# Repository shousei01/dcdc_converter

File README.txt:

DCDC converter - LLC (isolated) + 4-switch buck-boost, STM32G474RBT3          Rev E2 (2026-10-20)
12-48 V in, 1.5-48 V / 5 A / 50 W out, basic isolation, isolated CAN

01_hardware
  kicad_project\   KiCad 6/7 project (10-sheet wired schematic + routed 4-layer PCB). Open in KiCad, or import
                   into EasyEDA Pro (File > Import > KiCad) - same files as easyeda\*.zip
  easyeda\         DCDC_LLC_4SBB_G474_EasyEDA_import.zip
  docs\            DCDC_Design_Notes.docx / .pdf (design notes: sizing, full scales, firmware notes, review),
                   schematic PDF, PCB layer PDF, DRC report, pin-map.xlsx (every MCU pin + all AFs + what we use),
                   T1_PQ2620_winding_guide.html (hand-winding guide, 2D/3D, dots), layout_review_layers.png
  fabrication\     JLCPCB Gerber/drill zip, CPL (pick & place), JLCPCB BOM;
                   DCDC_JLC_BOM.csv / DCDC_JLC_CPL.csv = assembly upload files (U1, T1, connectors, headers,
                   SW1 and the J6 SWD pads are hand-soldered / not placed and left out)
  bom\             grouped BOM with prices / sources
02_firmware        firmware workspace + README (pin map, clocks, ADC full scales, VIN monitor, OVP, start-up)
03_calculations    loss / LLC sizing scripts; aux_fuse_check.py (Rev D); flyback_aux.py (Rev E isolated aux
                   flyback: rail budget, DCM operating points, stresses, ripple, feedback); copper_check.py
                   (Rev E copper widths / losses of the high-current paths on the finished board)
04_scripts         generator, routing and clean-up scripts that build this release (Rev E layout: 04_scripts\pcb5)

Rev E2 changes (20 Oct)
  - Debug-port series resistors: R123-R128 47.5 Ohm 0402 (UNI-ROYAL 0402WGF475JTCE, C82290) in SWDIO, SWCLK,
    TP_DAC, TP_GPIO1, TP_GPIO2, NRST; R129 2 Ohm 0603 (FOJAN FRC0603F2R00TS, C2933191) from +3V3 to J6 pin 7 /
    J7 VTref (net PROG_3V3). Each sits on the MCU side of the J6 / J7 branch, put into the existing traces.
  - DRC clean-up: the 16 courtyard overlaps Rev E accepted (T1 / CR1-CR6 / R64, T2 / D8 / C94 / R116 / C95 /
    Q11 / R114, C98 / R122, C69 / U11, C34 / U1) are cleared by 0.05-2 mm moves with the tracks re-attached;
    the 4 silk-over-pad notices are gone too. DRC: 0 errors, 0 warnings, 0 unconnected (docs\DRC_report.txt).
  - Board-edit scripts: 04_scripts\pcb6 (build_e2.sh lists the order).

Rev E changes
  - Isolated aux supply: the isolator's built-in 3.3 V is gone. New flyback (sheet "Isolated aux flyback"):
    UC3843B U20 from +10V_P, FDN86246 Q11, PA3855.006NLT EP13 transformer T2 (Np:Ns 1.33:1, 2250 Vdc hi-pot),
    SS110 D9 -> isolated +10 V. Secondary regulation: TL431 U22 (+10 V = 9.98 V) driving an EL357N opto U21
    into the UC3843 COMP pin; RCD clamp D8/R116/C94; 2 A primary current limit (R114 0.5 Ohm).
  - Secondary rails now come from the flyback, not VBUS: +10 V (drivers) -> U4 LMR16006 10 V -> 5 V ->
    U5 TLV75533 -> +3V3 (MCU, CAN, isolator side B) -> FB1 -> +3V3A. The MCU, CAN and drivers are up as soon
    as VIN is present, before the LLC starts.
  - U12 is now a CA-IS3742LW (4-channel isolator, no power). U12 ENA = +5V_P, ENB = +3V3.
  - VREF+ back to +3V3A (3.3 V); REF3030 U19 removed. Full scales: VBUS / VOUT 68.0 V, IL +/-20.6 A
    (zero 1.65 V), IOUT 6.6 A, DAC3 / COMP 0-3.3 V (see design notes and 02_firmware README).
  - PCB re-placed and re-routed for 1 oz outer / 0.5 oz inner copper: power on F.Cu pours (one net each),
    In1 solid ground planes (GNDP / GND / GND_ISO) with 4 mm isolation bands, VBUS link / VOUT strip / PGND bar
    copy on B.Cu, signals on In2 / B.Cu under ground floods. Gate loops as tight HO + HS pairs (0.4 mm) on
    B.Cu / In2; power via fields at 1.7 mm pitch so In1 keeps a ground web; own GND via on every small R/C in the
    MCU area. Board copper loss ~0.5 W at 50 W / 12 V in (03_calculations\copper_check.txt).
PCB status: 160 x 105 mm, 4 layers, 291 footprints, 779 vias; 0 DRC errors / 0 warnings / 0 unconnected with the
JLC rules loaded (docs\DRC_report.txt); no copper in the primary-secondary or CAN bands.
Order: 4 layers, 1.6 mm, 1 oz outer / 0.5 oz inner copper, JLC04161H-7628 stack-up;
upload fabrication\*_gerbers_JLCPCB.zip, DCDC_JLC_BOM.csv and DCDC_JLC_CPL.csv.
New parts to check in the JLC placement viewer: U20 (SOIC-8), U21 (SOP-4), U22 (SOT-23), Q11 (SOT-23),
T2 (EP13 SMD), U12 (SOIC-16W), U5 (SOT-23-5).

Rev D changes (history)
  - NTC moved PA4 -> PA6 (ADC2_IN3); PA4 kept free for DAC1_OUT1
  - 10k pull-down to GND on every unused MCU pin (R90-R105; R93 is now the PA2 / VIN_PWM pull-down)
  - HSE crystal 16 MHz (Y1 + 12 pF C0G)
  - (superseded in Rev E) ADC / DAC / comparator reference: external REF3030 (U19, 3.000 V +/-0.2 %) on VREF+, no longer the
    isolator's 3.3 V rail. Full scales: VBUS / VOUT 61.8 V, IL +/-18.75 A, IOUT 6.0 A (see design notes)
  - Primary input OVP: TL431 + LMV331, trips 50.26 V rising / 49.83 V falling, through U12 isolator
    channel 1 -> PA15 (HRTIM1_FLT2)
  - Isolated VIN monitor: primary ramp (~200 Hz) + comparator PWM through U12 channel 2 -> PA2 (TIM15_CH1);
    divider R81/R82 0.1 %. Monitoring only, about +/-0.5 % after a two-point calibration
  - Test pads TP1-TP15 on rails / filtered signals only (no switch nodes)
  - T1 footprint fits the vendor PQ2620 and PQ2625 6+6 bobbins: 3.8 mm pitch inside each 3-pin group,
    7.5 mm between pins 3 and 4, 25.4 mm row-to-row, 1.2 mm holes
  - JP1 is a 2x2 header that switches both legs of the CAN split termination
  - Silkscreen: VIN+/-, VOUT+/-, CAN_H / CAN_L / CAN_GND, JP1 shunt boxes, J7 notch + pin 1, DIP A0-A5 / ON=1
  - F1 now a 1206 7 A 63 V chip fuse (Littelfuse 0458007.DR; 2nd source Schurter 3413.0326.11);
    L2 / L3 now 5040 shielded 47 uH (Sunlord SWPA5040S470MT; 2nd source Bourns SRN5040-470M,
    Taiyo Yuden NRS5040T470MMGK). EN_AUX re-routed, VIN track centred between the L3 pads.
    Every part carries a JLCPCB-checked LCSC number (design.py JLC_LCSC) in the BOMs, schematic and PCB
  - Layout review (18 Oct): smaller switch-node pours, tighter gate loops, Kelvin taps, output pour,
    straightened routing, 5 mm ground stitching
  - JLCPCB compliance (4-layer, 2 oz outer): PTH pad-to-track >= 0.28 mm, inner hole-to-copper >= 0.3 mm,
    silkscreen text >= 1.0 mm / 0.15 mm stroke; limits kept as custom DRC rules in kicad_project\*.kicad_dru
Rev D PCB status: 160 x 105 mm, 4 layers, 257 footprints, 0 DRC errors / warnings with the JLC rules loaded,
0 unconnected, primary-secondary copper gap 4.0 mm on every layer.
Rev D order: 4 layers, 1.6 mm, 2 oz outer copper, JLC04161H-7628 stack-up; upload fabrication\*_gerbers_JLCPCB.zip.

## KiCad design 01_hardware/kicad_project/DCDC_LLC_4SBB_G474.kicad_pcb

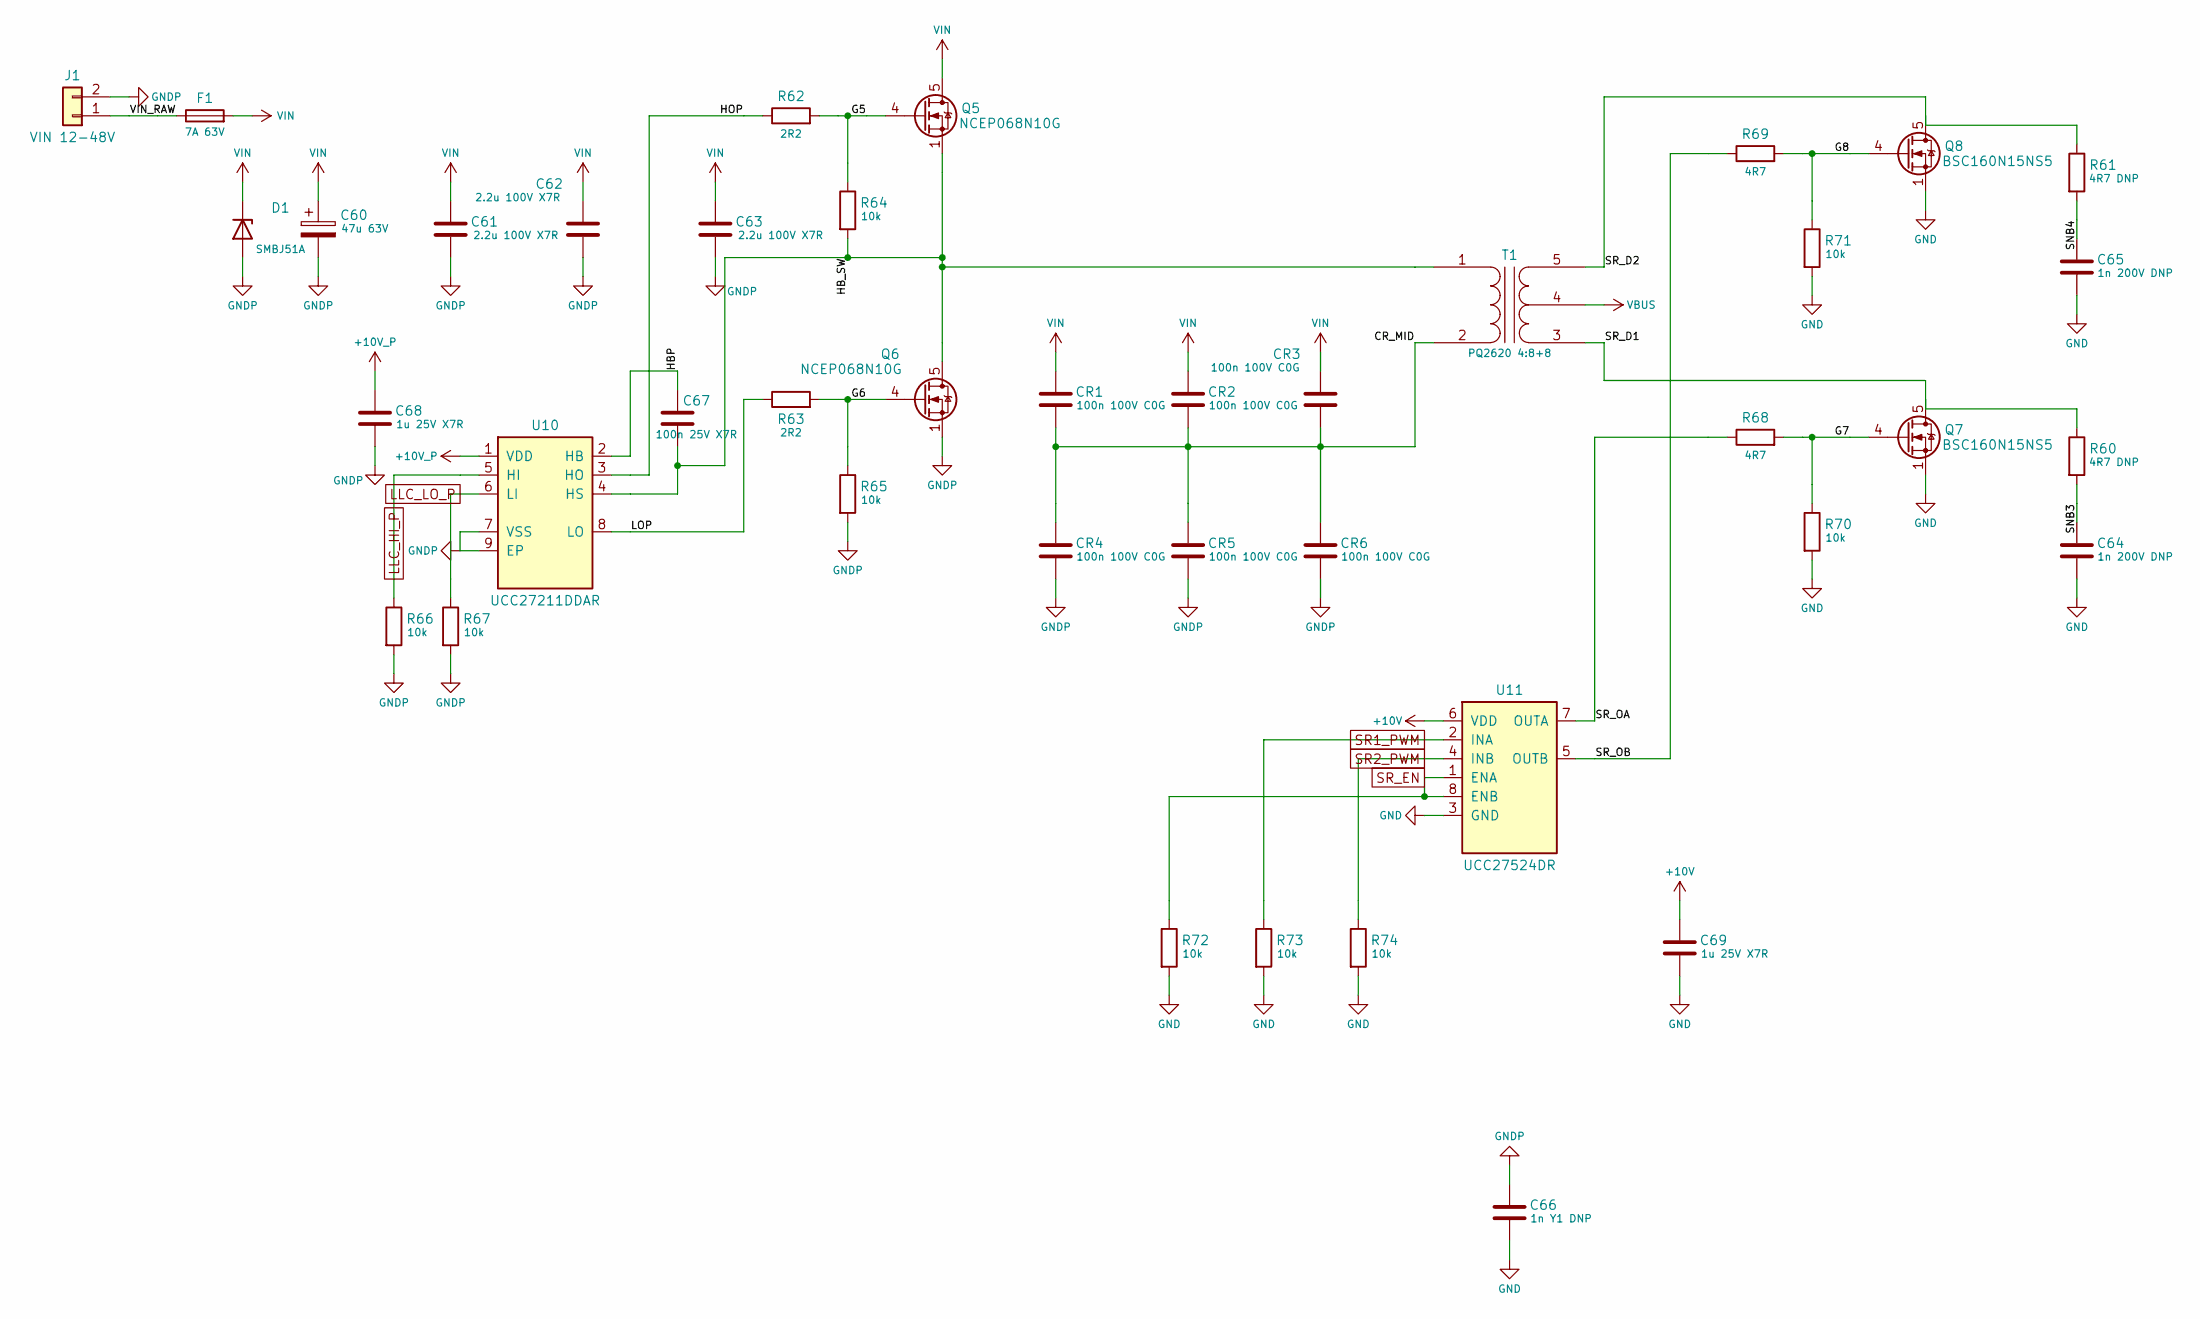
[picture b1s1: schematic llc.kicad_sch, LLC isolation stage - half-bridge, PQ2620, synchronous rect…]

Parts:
C60: 47u 63V; CP_Elec_10x10.5; MPN 47u 63V; LCSC C249664
C61, C62, C63: 2.2u 100V X7R; C_1210_3225Metric; MPN 2.2u 100V X7R; LCSC C153036
C64, C65: 1n 200V DNP; C_0805_2012Metric; MPN 1n 200V DNP
C66: 1n Y1 DNP; C_Disc_D8.0mm_W5.0mm_P7.50mm; MPN 1n Y1 DNP
C67: 100n 25V X7R; C_0603_1608Metric; MPN 100n 25V X7R; LCSC C14663
C68, C69: 1u 25V X7R; C_0603_1608Metric; MPN 1u 25V X7R; LCSC C15849
CR1, CR2, CR3, CR4, CR5, CR6: 100n 100V C0G; C_1206_3216Metric; MPN 100n 100V C0G; LCSC C2940749
D1: SMBJ51A; D_SMB; MPN SMBJ51A; LCSC C20883337
F1: 7A 63V; Fuse_1206_3216Metric; MPN 0458007.DR; LCSC C206980
J1: VIN 12-48V; PhoenixContact_MSTBA_2,5_2-G-5,08_1x02_P5.08mm_Horizontal; MPN KF2EDGR-5.08-2P; LCSC C441204
Q5, Q6: NCEP068N10G; TDSON-8-1; MPN NCEP068N10G; LCSC C503061
Q7, Q8: BSC160N15NS5; TDSON-8-1; MPN BSC160N15NS5; LCSC C459172
R60, R61: 4R7 DNP; R_1206_3216Metric; MPN 4R7 DNP
R62, R63: 2R2; R_0603_1608Metric; MPN 2R2; LCSC C2907006
R64, R65, R66, R67, R70, R71, R72, R73, R74: 10k; R_0402_1005Metric; MPN 10k; LCSC C2906861
R68, R69: 4R7; R_0603_1608Metric; MPN 4R7; LCSC C23164
T1: PQ2620 4:8+8; TX_PQ2620_12P; MPN PQ2620 4:8+8
U10: UCC27211DDAR; SOIC-8-1EP_3.9x4.9mm_P1.27mm_EP2.41x3.3mm; MPN UCC27211DDAR; LCSC C141980
U11: UCC27524DR; SOIC-8_3.9x4.9mm_P1.27mm; MPN UCC27524DR; LCSC C465729

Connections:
+10V: C69.1, U11.6 (VDD); also elsewhere on the board
+10V_P: C68.1, U10.1 (VDD); also elsewhere on the board
CR_MID: CR1.2, CR2.2, CR3.2, CR4.1, CR5.1, CR6.1, T1.2 (AB)
G5: Q5.4 (G), R62.2, R64.1
G6: Q6.4 (G), R63.2, R65.1
G7: Q7.4 (G), R68.2, R70.1
G8: Q8.4 (G), R69.2, R71.1
GND: C64.2, C65.2, C66.2, C69.2, Q7.1 (S), Q7.2 (S), Q7.3 (S), Q8.1 (S), Q8.2 (S), Q8.3 (S), R70.2, R71.2, R72.2, R73.2, R74.2, U11.3 (GND); also elsewhere on the board
GNDP: C60.2, C61.2, C62.2, C63.2, C66.1, C68.2, CR4.2, CR5.2, CR6.2, D1.2 (A), J1.2, Q6.1 (S), Q6.2 (S), Q6.3 (S), R65.2, R66.2, R67.2, U10.7 (VSS), U10.9 (EP); also elsewhere on the board
HBP: C67.1, U10.2 (HB)
HB_SW: C67.2, Q5.1 (S), Q5.2 (S), Q5.3 (S), Q6.5 (D), R64.2, T1.1 (AA), U10.4 (HS)
HOP: R62.1, U10.3 (HO)
LLC_HI_P: R66.1, U10.5 (HI); also elsewhere on the board
LLC_LO_P: R67.1, U10.6 (LI); also elsewhere on the board
LOP: R63.1, U10.8 (LO)
SNB3: C64.1, R60.2
SNB4: C65.1, R61.2
SR1_PWM: R73.1, U11.2 (INA); also elsewhere on the board
SR2_PWM: R74.1, U11.4 (INB); also elsewhere on the board
SR_D1: Q7.5 (D), R60.1, T1.3 (SA)
SR_D2: Q8.5 (D), R61.1, T1.5 (SB)
SR_EN: R72.1, U11.1 (ENA), U11.8 (ENB); also elsewhere on the board
SR_OA: R68.1, U11.7 (OUTA)
SR_OB: R69.1, U11.5 (OUTB)
VBUS: T1.4 (SC); also elsewhere on the board
VIN: C60.1, C61.1, C62.1, C63.1, CR1.1, CR2.1, CR3.1, D1.1 (K), F1.2, Q5.5 (D); also elsewhere on the board
VIN_RAW: F1.1, J1.1

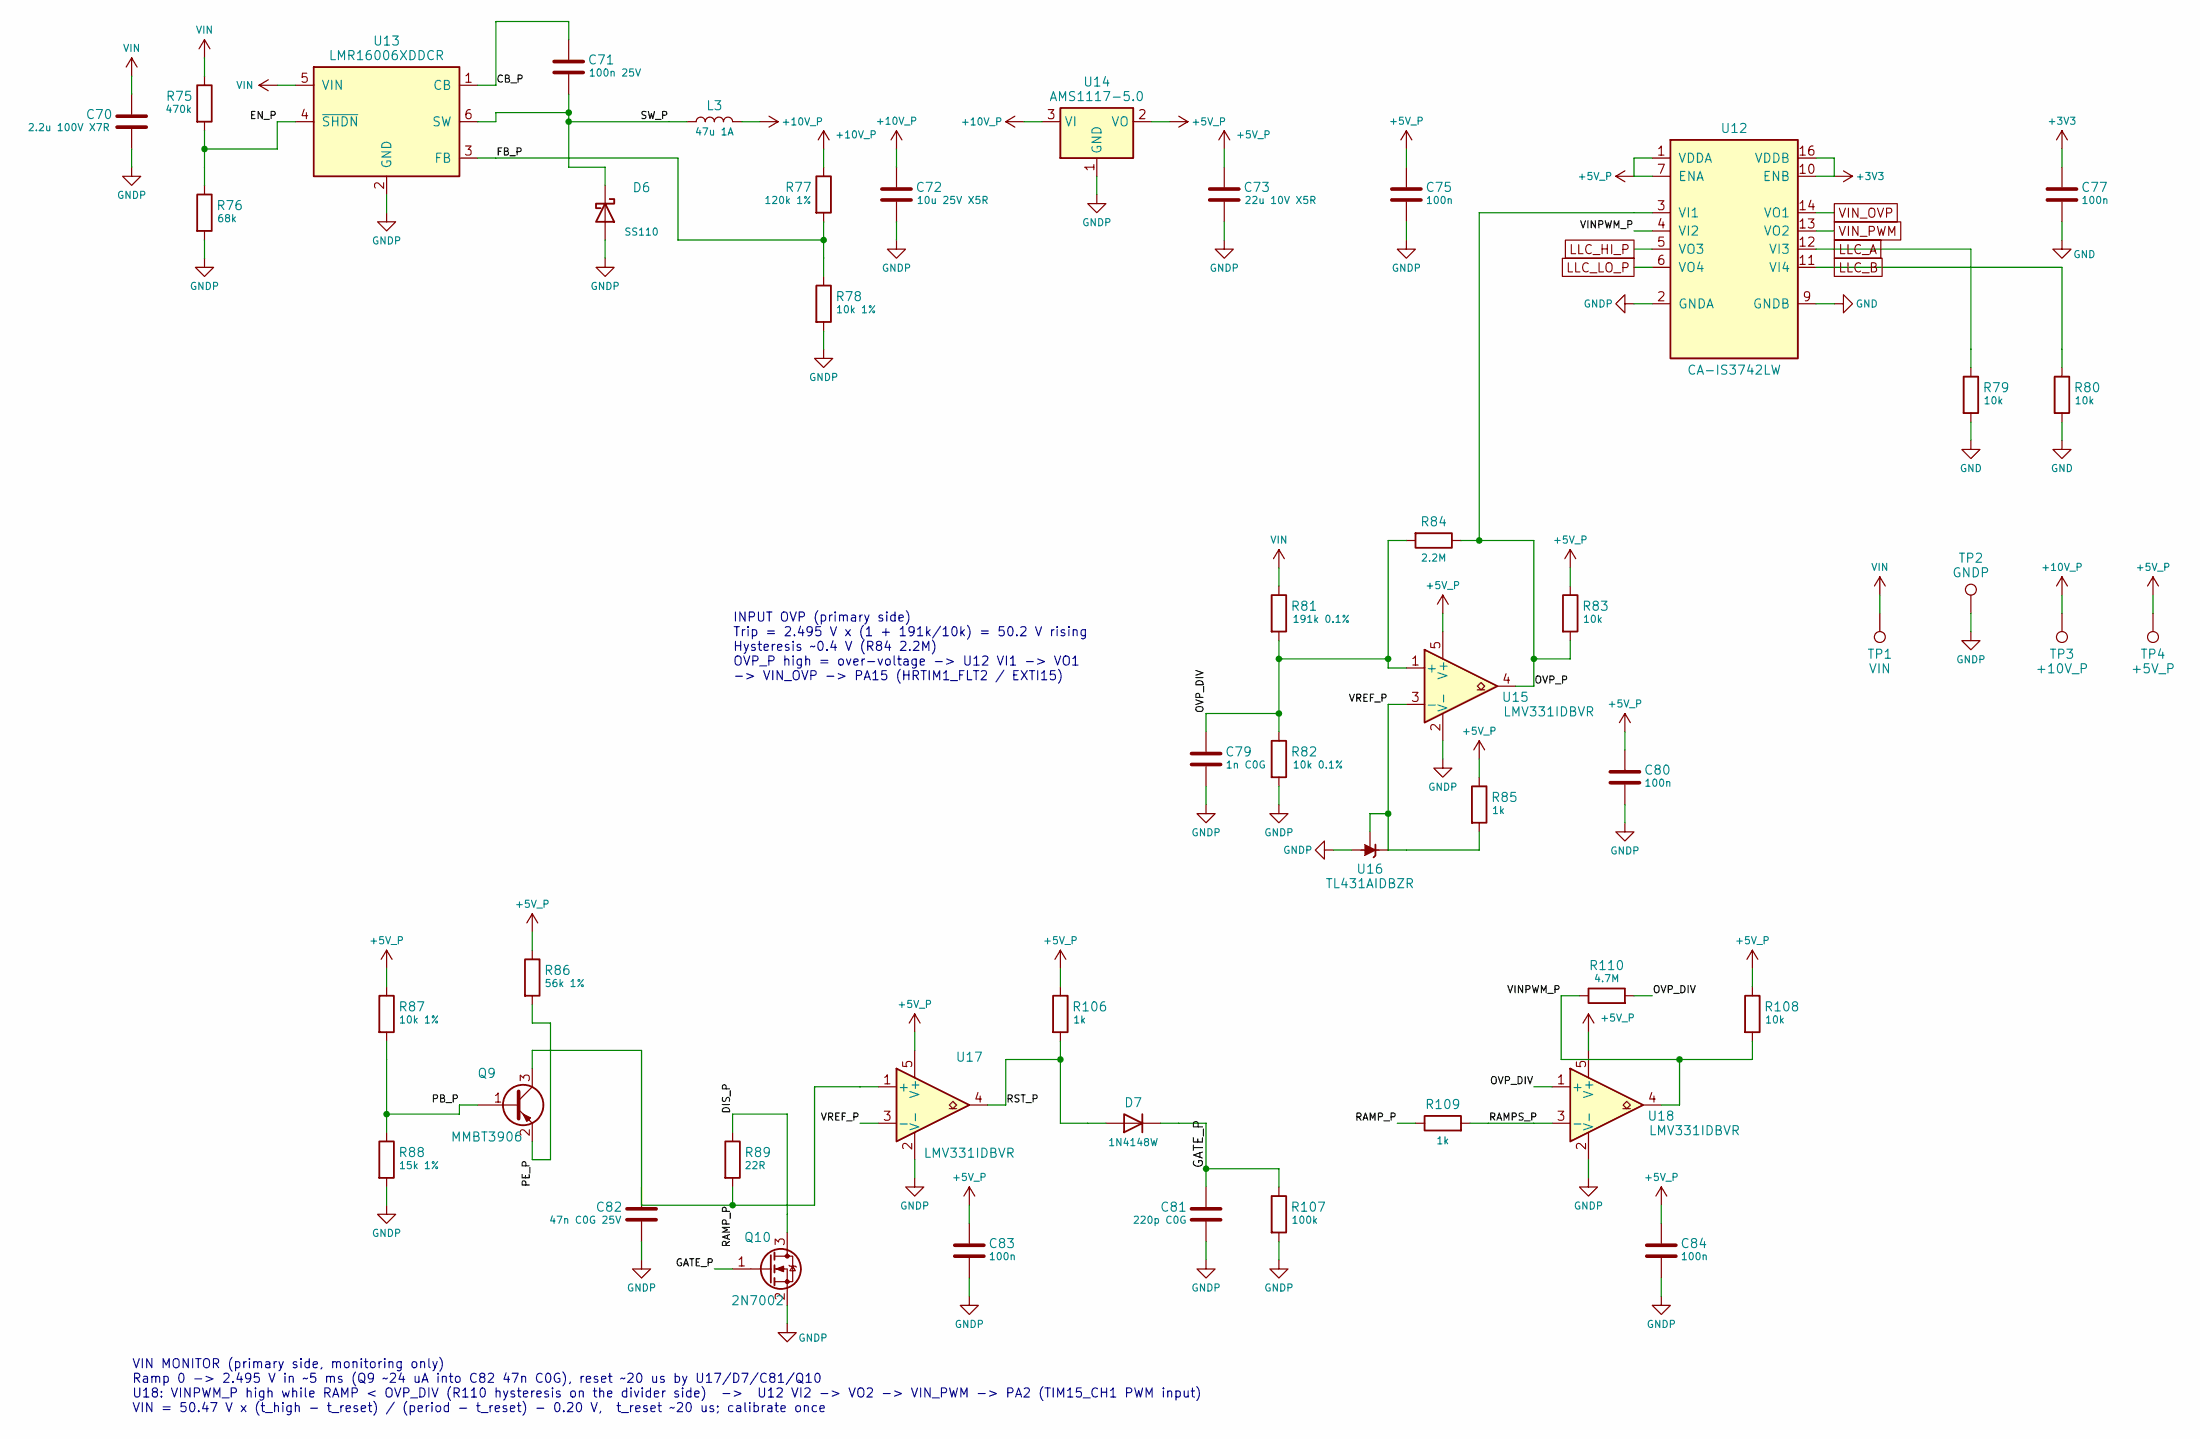
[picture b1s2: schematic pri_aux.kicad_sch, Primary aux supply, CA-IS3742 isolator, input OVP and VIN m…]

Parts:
C70: 2.2u 100V X7R; C_1210_3225Metric; MPN 2.2u 100V X7R; LCSC C153036
C71: 100n 25V; C_0402_1005Metric; MPN 100n 25V; LCSC C307331
C72: 10u 25V X5R; C_0805_2012Metric; MPN 10u 25V X5R; LCSC C15850
C73: 22u 10V X5R; C_0805_2012Metric; MPN 22u 10V X5R; LCSC C45783
C75, C77, C80, C83, C84: 100n; C_0402_1005Metric; MPN 100n; LCSC C307331
C79: 1n C0G; C_0402_1005Metric; MPN 1n C0G; LCSC C113780
C81: 220p C0G; C_0402_1005Metric; MPN 220p C0G; LCSC C107001
C82: 47n C0G 25V; C_0805_2012Metric; MPN C0805C473F3GECAUTO; LCSC C2233314
D6: SS110; D_SMA; MPN SS110; LCSC C2482
D7: 1N4148W; D_SOD-123; MPN 1N4148W; LCSC C81598
L3: 47u 1A; L_Sunlord_SWPA5040S; MPN FNR5040S470MT; LCSC C167974
Q9: MMBT3906; SOT-23; MPN MMBT3906; LCSC C53444
Q10: 2N7002; SOT-23; MPN 2N7002; LCSC C8545
R75: 470k; R_0603_1608Metric; MPN 470k; LCSC C23178
R76: 68k; R_0402_1005Metric; MPN 68k; LCSC C36871
R77: 120k 1%; R_0402_1005Metric; MPN 120k 1%; LCSC C25750
R78, R87: 10k 1%; R_0402_1005Metric; MPN 10k 1%; LCSC C2906861
R79, R80, R83, R108: 10k; R_0402_1005Metric; MPN 10k; LCSC C2906861
R81: 191k 0.1%; R_1206_3216Metric; MPN 191k 0.1%; LCSC C870479
R82: 10k 0.1%; R_0402_1005Metric; MPN 10k 0.1%; LCSC C844452
R84: 2.2M; R_0402_1005Metric; MPN 2.2M; LCSC C11490
R85, R106, R109: 1k; R_0402_1005Metric; MPN 1k; LCSC C11702
R86: 56k 1%; R_0402_1005Metric; MPN 56k 1%; LCSC C25796
R88: 15k 1%; R_0402_1005Metric; MPN 15k 1%; LCSC C25756
R89: 22R; R_0402_1005Metric; MPN 22R; LCSC C2929994
R107: 100k; R_0402_1005Metric; MPN 100k; LCSC C25741
R110: 4.7M; R_0402_1005Metric; MPN 4.7M; LCSC C227116
TP1: VIN; TestPoint_Pad_D1.5mm; MPN PCB pad, no part
TP2: GNDP; TestPoint_Pad_D1.5mm; MPN PCB pad, no part
TP3: +10V_P; TestPoint_Pad_D1.5mm; MPN PCB pad, no part
TP4: +5V_P; TestPoint_Pad_D1.5mm; MPN PCB pad, no part
U12: CA-IS3742LW; SOIC-16W_7.5x10.3mm_P1.27mm; MPN CA-IS3742LW; LCSC C4944981
U13: LMR16006XDDCR; SOT-23-6; MPN LMR16006XDDCR; LCSC C87080
U14: AMS1117-5.0; SOT-223-3_TabPin2; MPN AMS1117-5.0; LCSC C6187
U15, U17, U18: LMV331IDBVR; SOT-23-5; MPN LMV331IDBVR; LCSC C34731
U16: TL431AIDBZR; SOT-23; MPN TL431AIDBZR (TI pinout: 1 K, 2 REF, 3 A); LCSC C23892

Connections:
+3V3: C77.1, U12.10 (ENB), U12.16 (VDDB); also elsewhere on the board
+5V_P: C73.1, C75.1, C80.1, C83.1, C84.1, R83.1, R85.1, R86.1, R87.1, R106.1, R108.1, TP4.1, U12.1 (VDDA), U12.7 (ENA), U14.2 (VO), U15.5 (V+), U17.5 (V+), U18.5 (V+)
+10V_P: C72.1, L3.2, R77.1, TP3.1, U14.3 (VI); also elsewhere on the board
CB_P: C71.1, U13.1 (CB)
DIS_P: Q10.3 (D), R89.1
EN_P: R75.2, R76.1, U13.4 (~SHDN)
FB_P: R77.2, R78.1, U13.3 (FB)
GATE_P: C81.1, D7.1 (K), Q10.1 (G), R107.1
GND: C77.2, R79.2, R80.2, U12.9 (GNDB), U12.15 (GNDB); also elsewhere on the board
GNDP: C70.2, C72.2, C73.2, C75.2, C79.2, C80.2, C81.2, C82.2, C83.2, C84.2, D6.2 (A), Q10.2 (S), R76.2, R78.2, R82.2, R88.2, R107.2, TP2.1, U12.2 (GNDA), U12.8 (GNDA), U13.2 (GND), U14.1 (GND), U15.2 (V-), U16.3 (A), U17.2 (V-), U18.2 (V-); also elsewhere on the board
LLC_A: R79.1, U12.12 (VI3); also elsewhere on the board
LLC_B: R80.1, U12.11 (VI4); also elsewhere on the board
LLC_HI_P: U12.5 (VO3); also elsewhere on the board
LLC_LO_P: U12.6 (VO4); also elsewhere on the board
OVP_DIV: C79.1, R81.2, R82.1, R84.2, R110.2, U15.1 (+), U18.1 (+)
OVP_P: R83.2, R84.1, U12.3 (VI1), U15.4
PB_P: Q9.1 (B), R87.2, R88.1
PE_P: Q9.2 (E), R86.2
RAMPS_P: R109.2, U18.3 (-)
RAMP_P: C82.1, Q9.3 (C), R89.2, R109.1, U17.1 (+)
RST_P: D7.2 (A), R106.2, U17.4
SW_P: C71.2, D6.1 (K), L3.1, U13.6 (SW)
VIN: C70.1, R75.1, R81.1, TP1.1, U13.5 (VIN); also elsewhere on the board
VINPWM_P: R108.2, R110.1, U12.4 (VI2), U18.4
VIN_OVP: U12.14 (VO1); also elsewhere on the board
VIN_PWM: U12.13 (VO2); also elsewhere on the board
VREF_P: R85.2, U15.3 (-), U16.1 (K), U16.2 (REF), U17.3 (-)

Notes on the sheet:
INPUT OVP (primary side) Trip = 2.495 V x (1 + 191k/10k) = 50.2 V rising Hysteresis ~0.4 V (R84 2.2M) OVP_P high = over-voltage -> U12 VI1 -> VO1 -> VIN_OVP -> PA15 (HRTIM1_FLT2 / EXTI15)
VIN MONITOR (primary side, monitoring only) Ramp 0 -> 2.495 V in ~5 ms (Q9 ~24 uA into C82 47n C0G), reset ~20 us by U17/D7/C81/Q10 U18: VINPWM_P high while RAMP < OVP_DIV (R110 hysteresis on the divider side) -> U12 VI2 -> VO2 -> VIN_PWM -> PA2 (TIM15_CH1 PWM input) VIN = 50.47 V x (t_high - t_res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

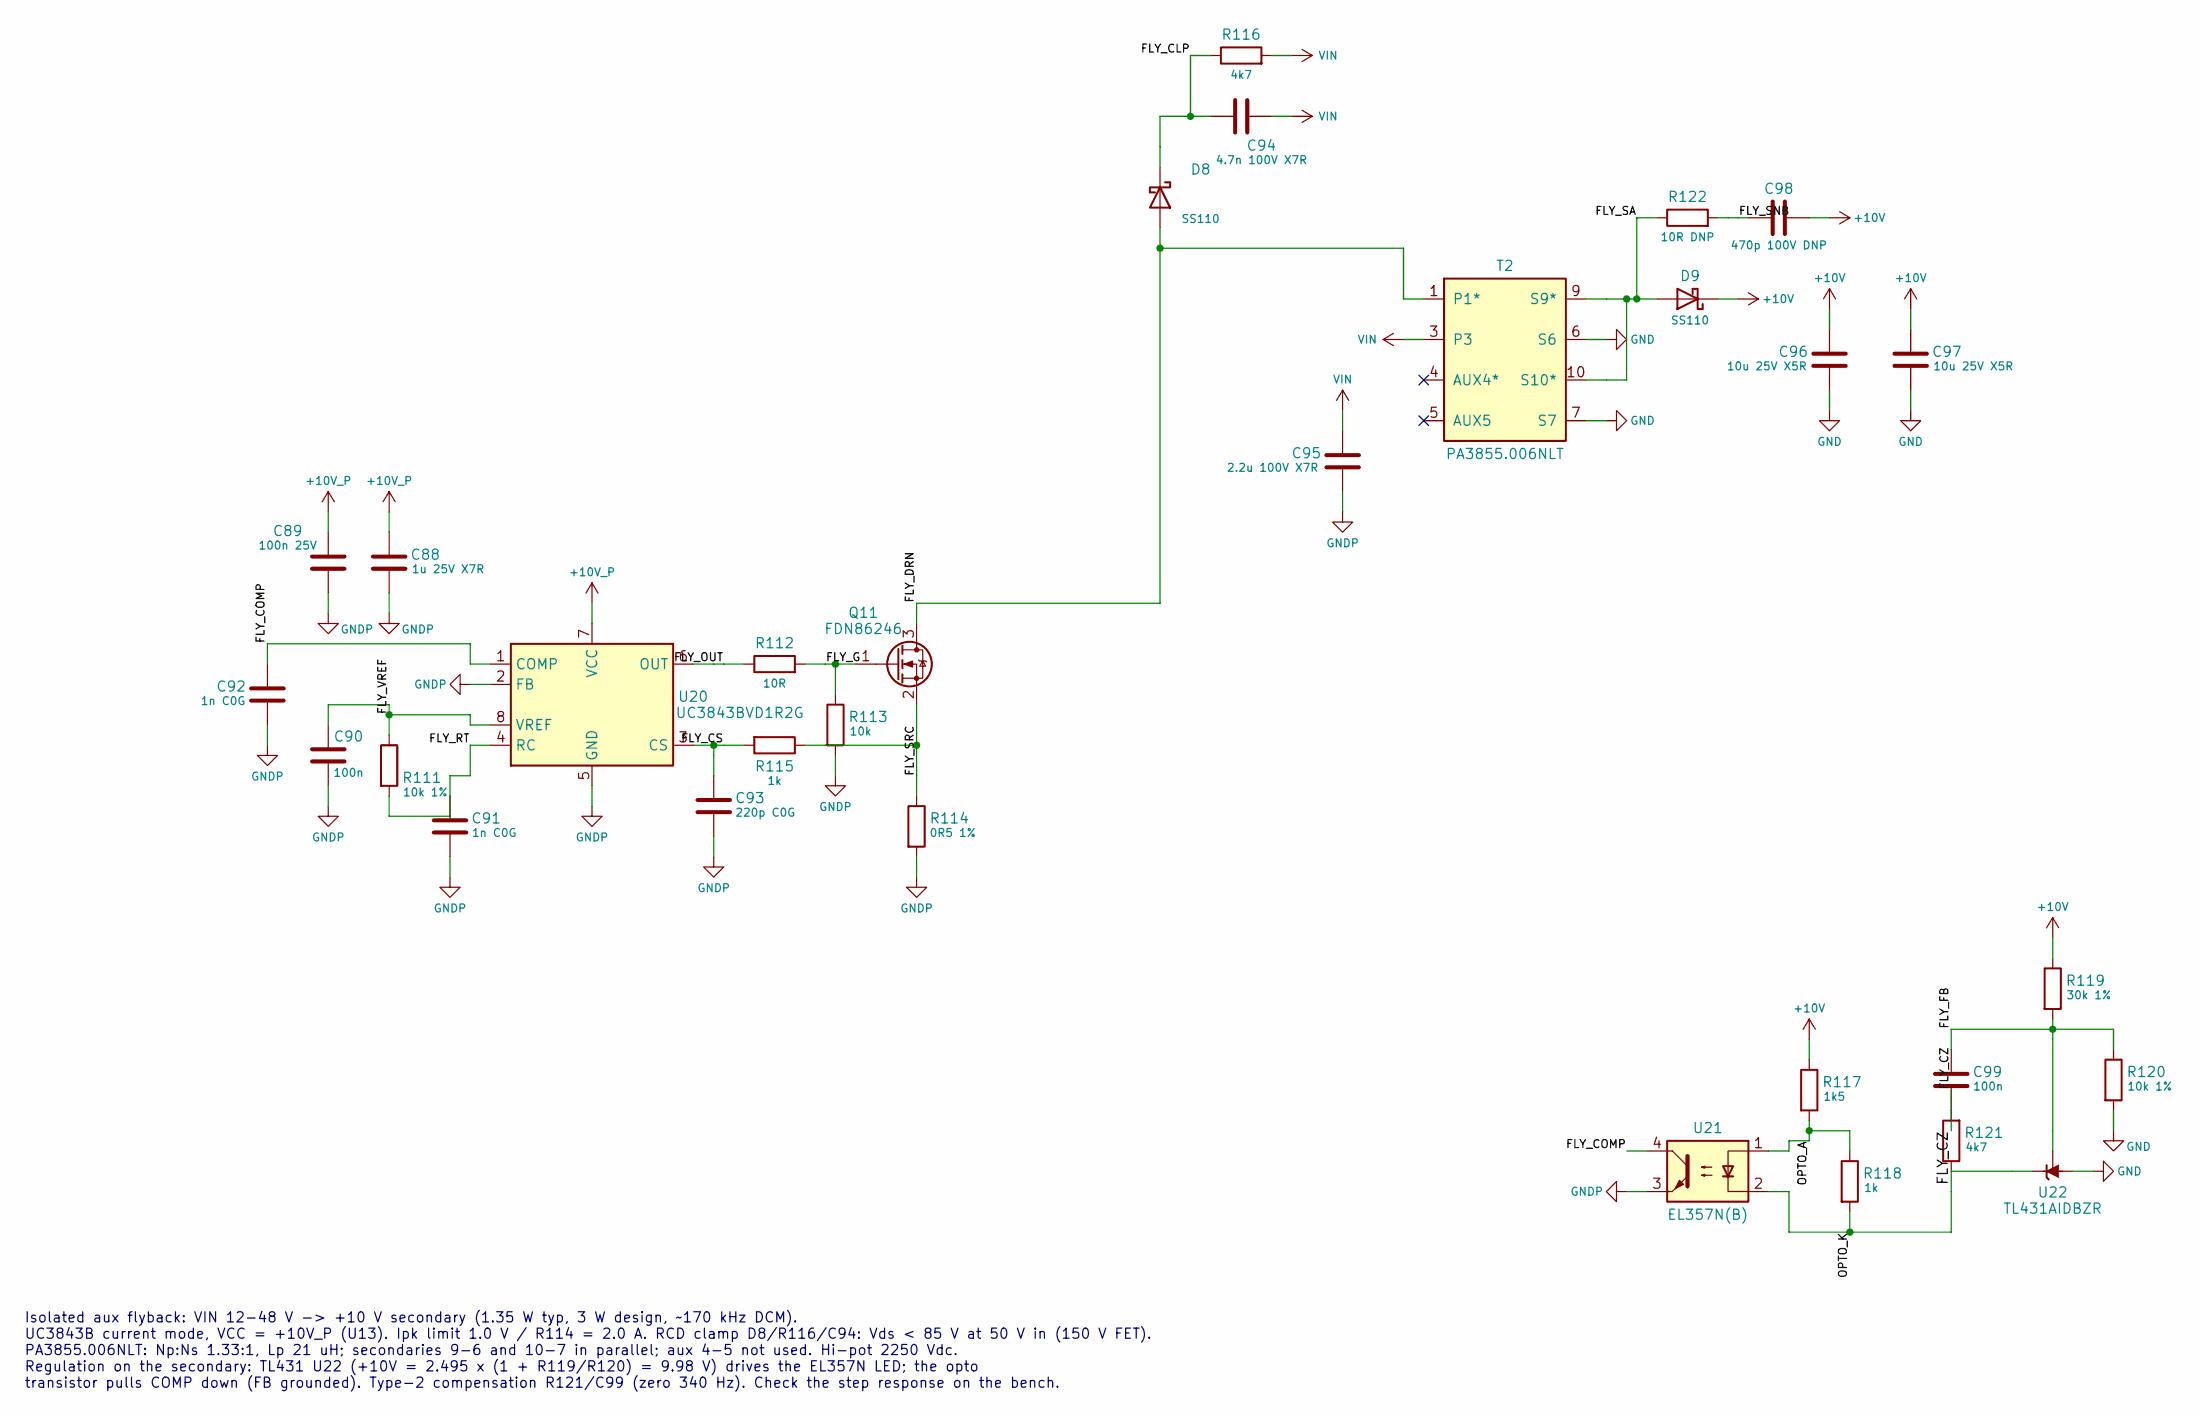
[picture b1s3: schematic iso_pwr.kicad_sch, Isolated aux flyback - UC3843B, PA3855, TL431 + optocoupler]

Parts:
C88: 1u 25V X7R; C_0603_1608Metric; MPN 1u 25V X7R; LCSC C15849
C89: 100n 25V; C_0402_1005Metric; MPN 100n 25V; LCSC C307331
C90, C99: 100n; C_0402_1005Metric; MPN 100n; LCSC C307331
C91, C92: 1n C0G; C_0402_1005Metric; MPN 1n C0G; LCSC C113780
C93: 220p C0G; C_0402_1005Metric; MPN 220p C0G; LCSC C107001
C94: 4.7n 100V X7R; C_0603_1608Metric; MPN 4.7n 100V X7R; LCSC C115052
C95: 2.2u 100V X7R; C_1210_3225Metric; MPN 2.2u 100V X7R; LCSC C153036
C96, C97: 10u 25V X5R; C_0805_2012Metric; MPN 10u 25V X5R; LCSC C15850
C98: 470p 100V DNP; C_0603_1608Metric; MPN 470p 100V DNP
D8, D9: SS110; D_SMA; MPN SS110; LCSC C2482
Q11: FDN86246; SOT-23; MPN FDN86246; LCSC C891118
R111, R120: 10k 1%; R_0402_1005Metric; MPN 10k 1%; LCSC C2906861
R112: 10R; R_0603_1608Metric; MPN 10R; LCSC C22859
R113: 10k; R_0402_1005Metric; MPN 10k; LCSC C2906861
R114: 0R5 1%; R_1206_3216Metric; MPN 0R5 1%; LCSC C25340
R115, R118: 1k; R_0402_1005Metric; MPN 1k; LCSC C11702
R116: 4k7; R_1206_3216Metric; MPN 4k7; LCSC C17936
R117: 1k5; R_0402_1005Metric; MPN 1k5; LCSC C25867
R119: 30k 1%; R_0402_1005Metric; MPN 30k 1%; LCSC C25776
R121: 4k7; R_0402_1005Metric; MPN 4k7; LCSC C25900
R122: 10R DNP; R_0603_1608Metric; MPN 10R DNP
T2: PA3855.006NLT; TX_PA3855_EP13_10P; MPN PA3855.006NLT; LCSC C5718384
U20: UC3843BVD1R2G; SOIC-8_3.9x4.9mm_P1.27mm; MPN UC3843BVD1R2G; LCSC C231572
U21: EL357N(B); SOP-4_3.8x4.1mm_P2.54mm; MPN EL357N(B)(TA)-G; LCSC C42381015
U22: TL431AIDBZR; SOT-23; MPN TL431AIDBZR; LCSC C23892

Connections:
+10V: C96.1, C97.1, C98.2, D9.1 (K), R117.1, R119.1; also elsewhere on the board
+10V_P: C88.1, C89.1, U20.7 (VCC); also elsewhere on the board
FLY_CLP: C94.1, D8.1 (K), R116.1
FLY_COMP: C92.1, U20.1 (COMP), U21.4
FLY_CS: C93.1, R115.2, U20.3 (CS)
FLY_CZ: C99.1, R121.2
FLY_DRN: D8.2 (A), Q11.3 (D), T2.1 (P1*)
FLY_FB: C99.2, R119.2, R120.1, U22.2 (REF)
FLY_G: Q11.1 (G), R112.2, R113.1
FLY_OUT: R112.1, U20.6 (OUT)
FLY_RT: C91.1, R111.2, U20.4 (RC)
FLY_SA: D9.2 (A), R122.1, T2.9 (S9*), T2.10 (S10*)
FLY_SNB: C98.1, R122.2
FLY_SRC: Q11.2 (S), R114.1, R115.1
FLY_VREF: C90.1, R111.1, U20.8 (VREF)
GND: C96.2, C97.2, R120.2, T2.6 (S6), T2.7 (S7), U22.3 (A); also elsewhere on the board
GNDP: C88.2, C89.2, C90.2, C91.2, C92.2, C93.2, C95.2, R113.2, R114.2, U20.2 (FB), U20.5 (GND), U21.3; also elsewhere on the board
OPTO_A: R117.2, R118.1, U21.1
OPTO_K: R118.2, R121.1, U21.2, U22.1 (K)
VIN: C94.2, C95.1, R116.2, T2.3; also elsewhere on the board

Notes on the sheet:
Isolated aux flyback: VIN 12-48 V -> +10 V secondary (1.35 W typ, 3 W design, ~170 kHz DCM). UC3843B current mode, VCC = +10V_P (U13). Ipk limit 1.0 V / R114 = 2.0 A. RCD clamp D8/R116/C94: Vds < 85 V at 50 V in (150 V FET). PA3855.006NLT: Np:Ns 1.33:1, Lp 21 uH; secondaries 9-6 and 10-7 in paralle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

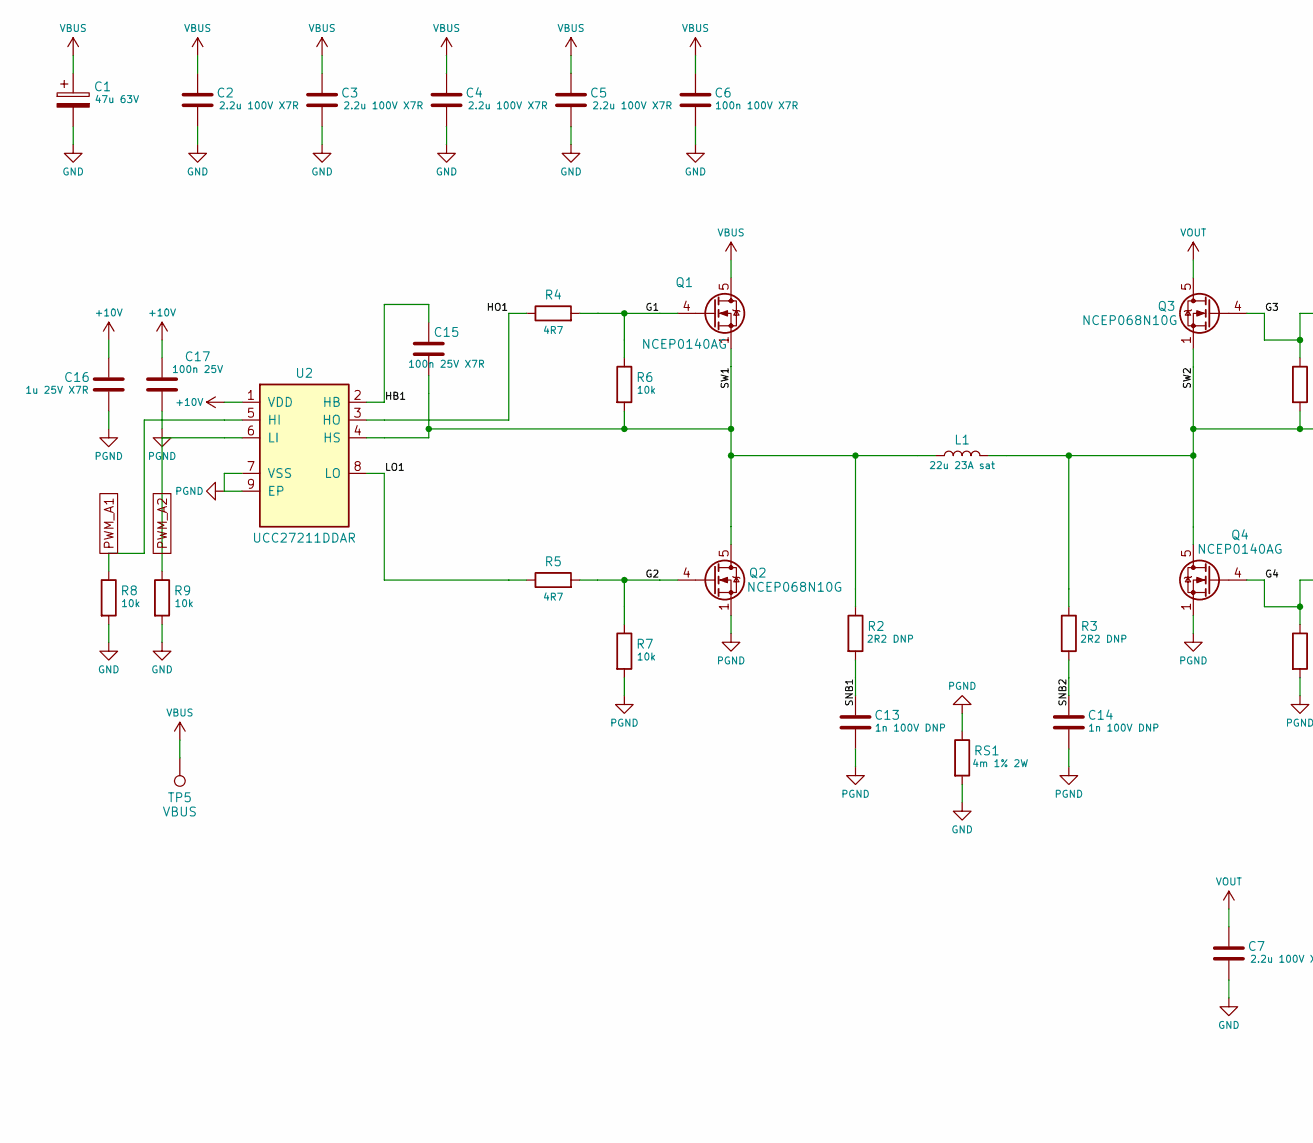
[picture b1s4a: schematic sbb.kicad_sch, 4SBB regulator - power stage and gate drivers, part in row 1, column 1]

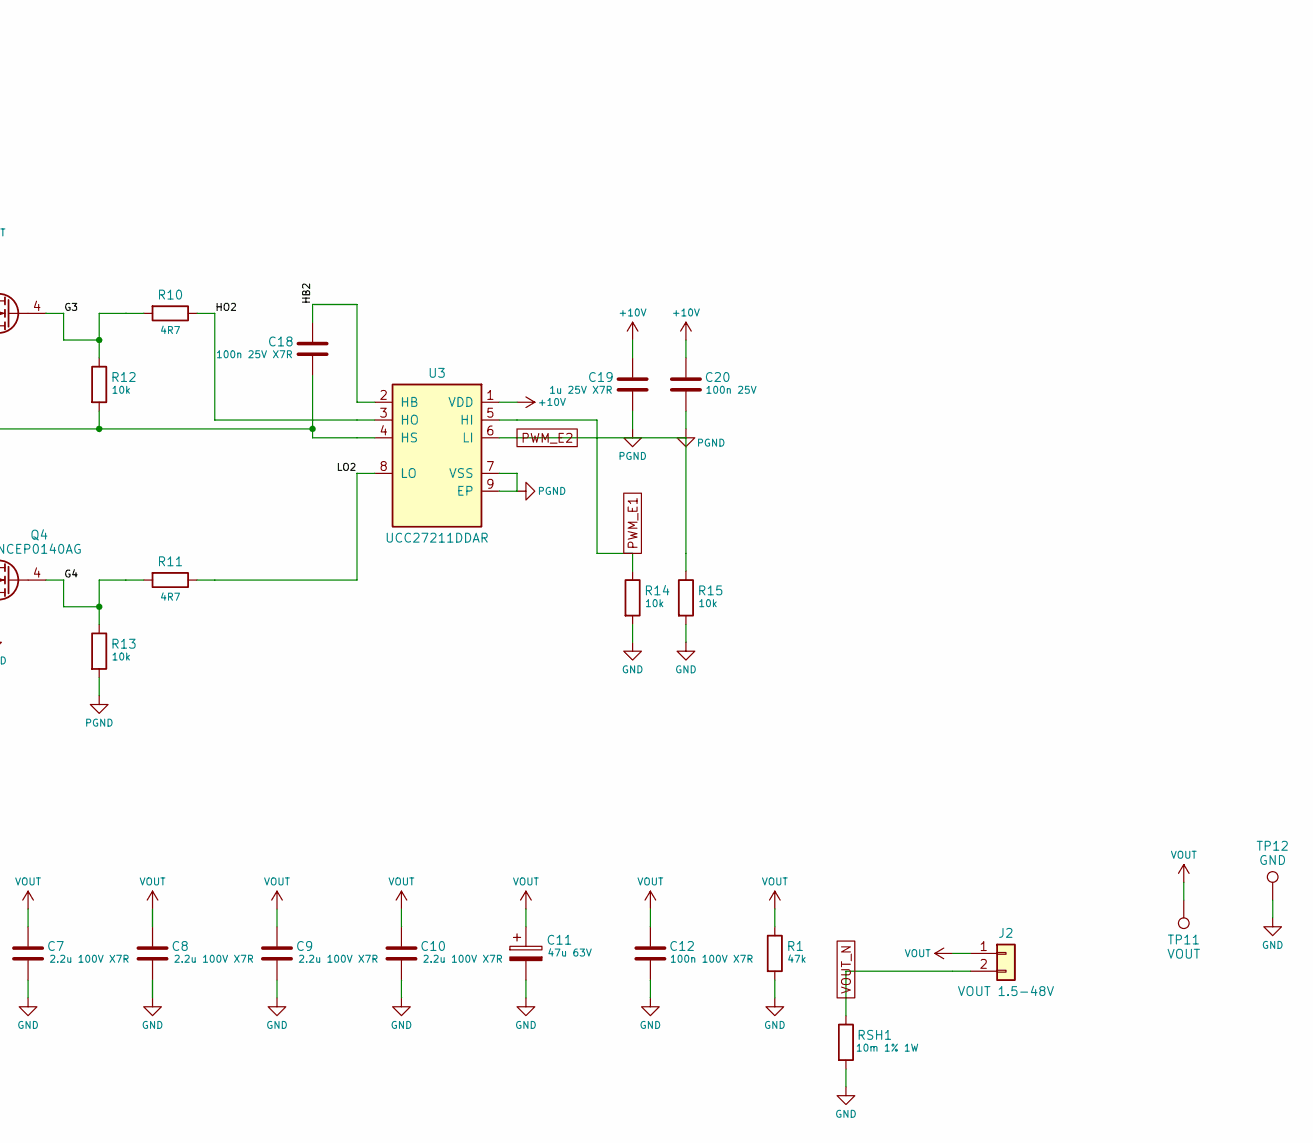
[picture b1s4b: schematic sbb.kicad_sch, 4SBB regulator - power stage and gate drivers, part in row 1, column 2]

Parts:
C1, C11: 47u 63V; CP_Elec_10x10.5; MPN 47u 63V; LCSC C249664
C2, C3, C4, C5, C7, C8, C9, C10: 2.2u 100V X7R; C_1210_3225Metric; MPN 2.2u 100V X7R; LCSC C153036
C6, C12: 100n 100V X7R; C_0603_1608Metric; MPN 100n 100V X7R; LCSC C88219
C13, C14: 1n 100V DNP; C_0603_1608Metric; MPN 1n 100V DNP
C15, C18: 100n 25V X7R; C_0603_1608Metric; MPN 100n 25V X7R; LCSC C14663
C16, C19: 1u 25V X7R; C_0603_1608Metric; MPN 1u 25V X7R; LCSC C15849
C17, C20: 100n 25V; C_0402_1005Metric; MPN 100n 25V; LCSC C307331
J2: VOUT 1.5-48V; PhoenixContact_MSTBA_2,5_2-G-5,08_1x02_P5.08mm_Horizontal; MPN KF2EDGR-5.08-2P; LCSC C441204
L1: 22u 23A sat; L_Bourns_SRP1770TA_16.9x16.9mm; MPN PSPMAA1770-220M-CGP; LCSC C49308184
Q1, Q4: NCEP0140AG; TDSON-8-1; MPN NCEP0140AG; LCSC C503009
Q2, Q3: NCEP068N10G; TDSON-8-1; MPN NCEP068N10G; LCSC C503061
R1: 47k; R_1206_3216Metric; MPN 47k; LCSC C2907507
R2, R3: 2R2 DNP; R_1206_3216Metric; MPN 2R2 DNP
R4, R5, R10, R11: 4R7; R_0603_1608Metric; MPN 4R7; LCSC C23164
R6, R7, R8, R9, R12, R13, R14, R15: 10k; R_0402_1005Metric; MPN 10k; LCSC C2906861
RS1: 4m 1% 2W; R_2512_6332Metric; MPN HoJLR2512-3W-4mR-1%; LCSC C2904236
RSH1: 10m 1% 1W; R_2512_6332Metric; MPN 10m 1% 1W; LCSC C500718
TP5: VBUS; TestPoint_Pad_D1.5mm; MPN PCB pad, no part
TP11: VOUT; TestPoint_Pad_D1.5mm; MPN PCB pad, no part
TP12: GND; TestPoint_Pad_D1.5mm; MPN PCB pad, no part
U2, U3: UCC27211DDAR; SOIC-8-1EP_3.9x4.9mm_P1.27mm_EP2.41x3.3mm; MPN UCC27211DDAR; LCSC C141980

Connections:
+10V: C16.1, C17.1, C19.1, C20.1, U2.1 (VDD), U3.1 (VDD); also elsewhere on the board
G1: Q1.4 (G), R4.2, R6.1
G2: Q2.4 (G), R5.2, R7.1
G3: Q3.4 (G), R10.2, R12.1
G4: Q4.4 (G), R11.2, R13.1
GND: C1.2, C2.2, C3.2, C4.2, C5.2, C6.2, C7.2, C8.2, C9.2, C10.2, C11.2, C12.2, R1.2, R8.2, R9.2, R14.2, R15.2, RS1.2, RSH1.2, TP12.1; also elsewhere on the board
HB1: C15.1, U2.2 (HB)
HB2: C18.1, U3.2 (HB)
HO1: R4.1, U2.3 (HO)
HO2: R10.1, U3.3 (HO)
LO1: R5.1, U2.8 (LO)
LO2: R11.1, U3.8 (LO)
PGND: C13.2, C14.2, C16.2, C17.2, C19.2, C20.2, Q2.1 (S), Q2.2 (S), Q2.3 (S), Q4.1 (S), Q4.2 (S), Q4.3 (S), R7.2, R13.2, RS1.1, U2.7 (VSS), U2.9 (EP), U3.7 (VSS), U3.9 (EP); also elsewhere on the board
PWM_A1: R8.1, U2.5 (HI); also elsewhere on the board
PWM_A2: R9.1, U2.6 (LI); also elsewhere on the board
PWM_E1: R14.1, U3.5 (HI); also elsewhere on the board
PWM_E2: R15.1, U3.6 (LI); also elsewhere on the board
SNB1: C13.1, R2.2
SNB2: C14.1, R3.2
SW1: C15.2, L1.1, Q1.1 (S), Q1.2 (S), Q1.3 (S), Q2.5 (D), R2.1, R6.2, U2.4 (HS)
SW2: C18.2, L1.2, Q3.1 (S), Q3.2 (S), Q3.3 (S), Q4.5 (D), R3.1, R12.2, U3.4 (HS)
VBUS: C1.1, C2.1, C3.1, C4.1, C5.1, C6.1, Q1.5 (D), TP5.1; also elsewhere on the board
VOUT: C7.1, C8.1, C9.1, C10.1, C11.1, C12.1, J2.1, Q3.5 (D), R1.1, TP11.1; also elsewhere on the board
VOUT_N: J2.2, RSH1.1; also elsewhere on the board
